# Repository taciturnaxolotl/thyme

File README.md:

# The thyme keyboard

> [!NOTE]
> If you want to build this yourself then go grab the files from the latest release!

## BOM

| Part                                                    | Quantity                                                                        | Price    | Link                                                                                                            | Description                                                                                 | Notes                                                   |
| ------------------------------------------------------- | ------------------------------------------------------------------------------- | -------- | --------------------------------------------------------------------------------------------------------------- | ------------------------------------------------------------------------------------------- | ------------------------------------------------------- |
| PCB                                                     | 1                                                                               | `$15.70` | [JLCPCB](https://jlcpcb.com)                                                                                    | 2-layer, 1.6mm, black, leaded Hasl                                                          | I wanted to get ENIG but that bumped the price by `$20` |
| Total `$15.70` + `$13.04` shipping                      |                                                                                 |          |                                                                                                                 |                                                                                             |                                                         |
|                                                         |                                                                                 |          |                                                                                                                 |                                                                                             |                                                         |
| Choc v1 switches                                        | 50                                                                              | `$25.00` | [Chosfox](https://chosfox.com/products/kailh-chocs?variant=42514648006850)                                      | pink variant: `20+-5 gf` linear                                                             | `$0.50` per switch                                      |
| Choc PG1350                                             | 50                                                                              | `$7.25`  | [Chosfox](https://chosfox.com/products/kailh-choc-switch-1350-hot-swap-sockets)                                 | hot swap sockets                                                                            | `$0.145` per socket                                     |
| 1u keycaps                                              | 40                                                                              | `$14.00` | [Chosfox](https://chosfox.com/collections/low-profile-keycaps/products/chocfox-cfx-choc-keycaps)                | White PBT low profile                                                                       | `$0.35` per keycap                                      |
| 1u homing keycaps                                       | 2                                                                               | `$0.80`  | [Chosfox](https://chosfox.com/collections/low-profile-keycaps/products/chocfox-cfx-choc-keycaps)                | White PBT low profile                                                                       | `$0.40` per keycap                                      |
| 1.5u keycaps                                            | 2                                                                               | `$1.65`  | [Chosfox](https://chosfox.com/collections/low-profile-keycaps/products/chocfox-cfx-choc-keycaps)                | White PBT low profile                                                                       | `$0.83` per keycap                                      |
| Total cost: `$48.70` + `$8` shipping                    |                                                                                 |          |                                                                                                                 | average of `$0.37` per keycap                                                               |                                                         |
|                                                         |                                                                                 |          |                                                                                                                 |                                                                                             |                                                         |
| SuperMini NRF52840 (Nice!Nano footprint)                | 2                                                                               | `$8.08`  | [AliExpress](https://www.aliexpress.us/item/3256805848952479.html)                                              | Wireless Microcontroller                                                                    | `$4.04` per MCU                                         |
| 301230 3.7V 110mAh LiPo Battery                         | 2                                                                               | `$7.50`  | [AliExpress](https://www.aliexpress.us/item/2255799987926232.html)                                              | the non jst ones are cheaper but the crimper is 60 bucks and there is no way im buying that | `$3.75` per battery                                     |
| Diodes                                                  | 42                                                                              | `$0.99`  | [Aliexpress](https://www.aliexpress.us/item/2255800939822415.html)                                              | 1N4148                                                                                      | `$0.01` per diode                                       |
| Machine Pins                                            | 1                                                                               | `$0.99`  | [AliExpress](https://www.aliexpress.us/item/3256805556329561.html)                                              | 26x2 needed to socket the two MCUs                                                          | comes in a 100 pack of 4 per header                     |
| Total cost: `$14.10` + `$6.52` shipping                 |                                                                                 |          |                                                                                                                 |                                                                                             |                                                         |
|                                                         |                                                                                 |          |                                                                                                                 |                                                                                             |                                                         |
| Power Switch                                            | 4                                                                               | `$0.39`  | [DigiKey](https://www.digikey.com/en/products/detail/same-sky-formerly-cui-devices/SLW-1277744-3A-N-D/24399208) | added an extra switch for each side as backup                                               | `$0.10` per switch                                      |
| JST PH 2.0mm 2-pin Connector                            | 4                                                                               | `$0.40`  | [DigiKey](https://www.digikey.com/en/products/detail/jst-sales-america-inc/S2B-PH-K-S/926626)                   |                                                                                             | `$0.10` per connector                                   |
| Total cost: `$1.96` + `$8.15` tarrif/sales tax/shipping | i cant find good matches for these on ali and shipping is ridiculous rn as well |          |                                                                                                                 |                                                                                             |                                                         |
|                                                         |                                                                                 |          |                                                                                                                 |
| Machine Sockets 2.54mm                                  | 1                                                                               | `$7.35`  | [Amazon](https://www.amazon.com/dp/B08Y8RB4BH)                                                                  | 26x2 needed to socket the two MCUs                                                          | comes in a 10 pack of 40x1 rows                         |

Total cost: `$123.52`

### Shipping / Tax / Tariffs / Per store shopping list

| Store      | Shipping                      | Subtotal | Total    | Items                                                                       |
| ---------- | ----------------------------- | -------- | -------- | --------------------------------------------------------------------------- |
| AliExpress | `$6.52`                       | `$14.20` | `$20.62` | 2x SuperMini NRF52840, Machine Pins, 2x LiPo Battery, 42x diodes            |
| DigiKey    | `$8.15` (tarrifs and tax too) | `$1.96`  | `$10.11` | 4x Power Switch, 4x JST Connector                                           |
| Chosfox    | `$8`                          | `$48.70` | `$56.70` | 50x Choc v1 switches, 40x 1u keycaps, 2x 1u homing keycaps, 2x 1.5u keycaps |
| JLCPCB     | `$13.04`                      | `$15.70` | `$28.74` | 1x PCB                                                                      |
| Amazon     | `$0`                          | `7.35`   | `$7.35`  | machine sockets                                                             |

## Schematics

## Build Notes

Panelization is the most annoying bit of this whole process. I was able to finally get it work work by using [`kikit`](https://yaqwsx.github.io/KiKit/latest/installation/intro/) to generate rails and tabs.

```bash
kikit panelize \
    --layout 'grid; rows: 1; cols: 1; space: 3mm;' \
    --tabs 'fixed; width: 3mm; vcount: 8;' \
    --cuts 'mousebites; drill: 0.5mm; spacing: 1mm; offset: 0.2mm; prolong: 0.5mm;' \
    --framing 'railstb; width: 5mm; space: 3mm; chamfer: 1mm;' \
    --tooling '3hole; hoffset: 2.5mm; voffset: 2.5mm; size: 1.5mm;' \
    --fiducials '3fid; hoffset: 5mm; voffset: 2.5mm; coppersize: 2mm; opening: 1mm;' \
    --post 'millradius: 1mm;' \
    --text 'simple; text: "THYME v1.14"; anchor: mt; voffset: 2mm;' \
    --text2 'simple; text: Created on {date} JLC Order: JLCJLCJLC; anchor: mb; voffset: -2.5mm; hjustify: center; vjustify: center;' \
    thyme.kicad_pcb panelization/panelized.kicad_pcb
```

Firmware is `zmk` and is maintained in the submodule [/zmk](https://github.com/taciturnaxolotl/thyme-module). The latest firmware build can be grabbed from [nightly.link/taciturnaxolotl/thyme-module/workflows/build](https://nightly.link/taciturnaxolotl/thyme-module/workflows/build/main) as a zip containing the left and right half `uf2` files.

The case was made in onshape and is available in [this document](https://cad.onshape.com/documents/eb30178d0af4291efc746ab6/w/0d165c7d0bf8d717a9598c9f/e/3dd4b0baac9c9ef14c8041ba?renderMode=0&uiState=67efb22294ee2703b96c81ea). The case is made of PLA and printed on an A1 mini. It is likely to change quite a bit once I get my pcb assembled and can fit test stuff. Evenentually I would like to add a top plate that attaches to the bottom with magnets and mill the whole case out of aluminum.

A major tool that helped with the research and organization of my thoughts was my [figjam board](https://www.figma.com/board/wyCQS9SeIG2Sutu5v6OT2m/thyme---split-mech-keyboard?node-id=0-1&t=SG0VuRAT0FkSCQlS-1)! I used it to keep track of all the resources I found and what parts I wanted to use. Once I got to actually picking specific parts I moved that to the bom table above.

<p align="center">
	<i><code>&copy 2025-present <a href="https://github.com/taciturnaxolotl">Kieran Klukas</a></code></i>
</p>

<p align="center">
	
</p>

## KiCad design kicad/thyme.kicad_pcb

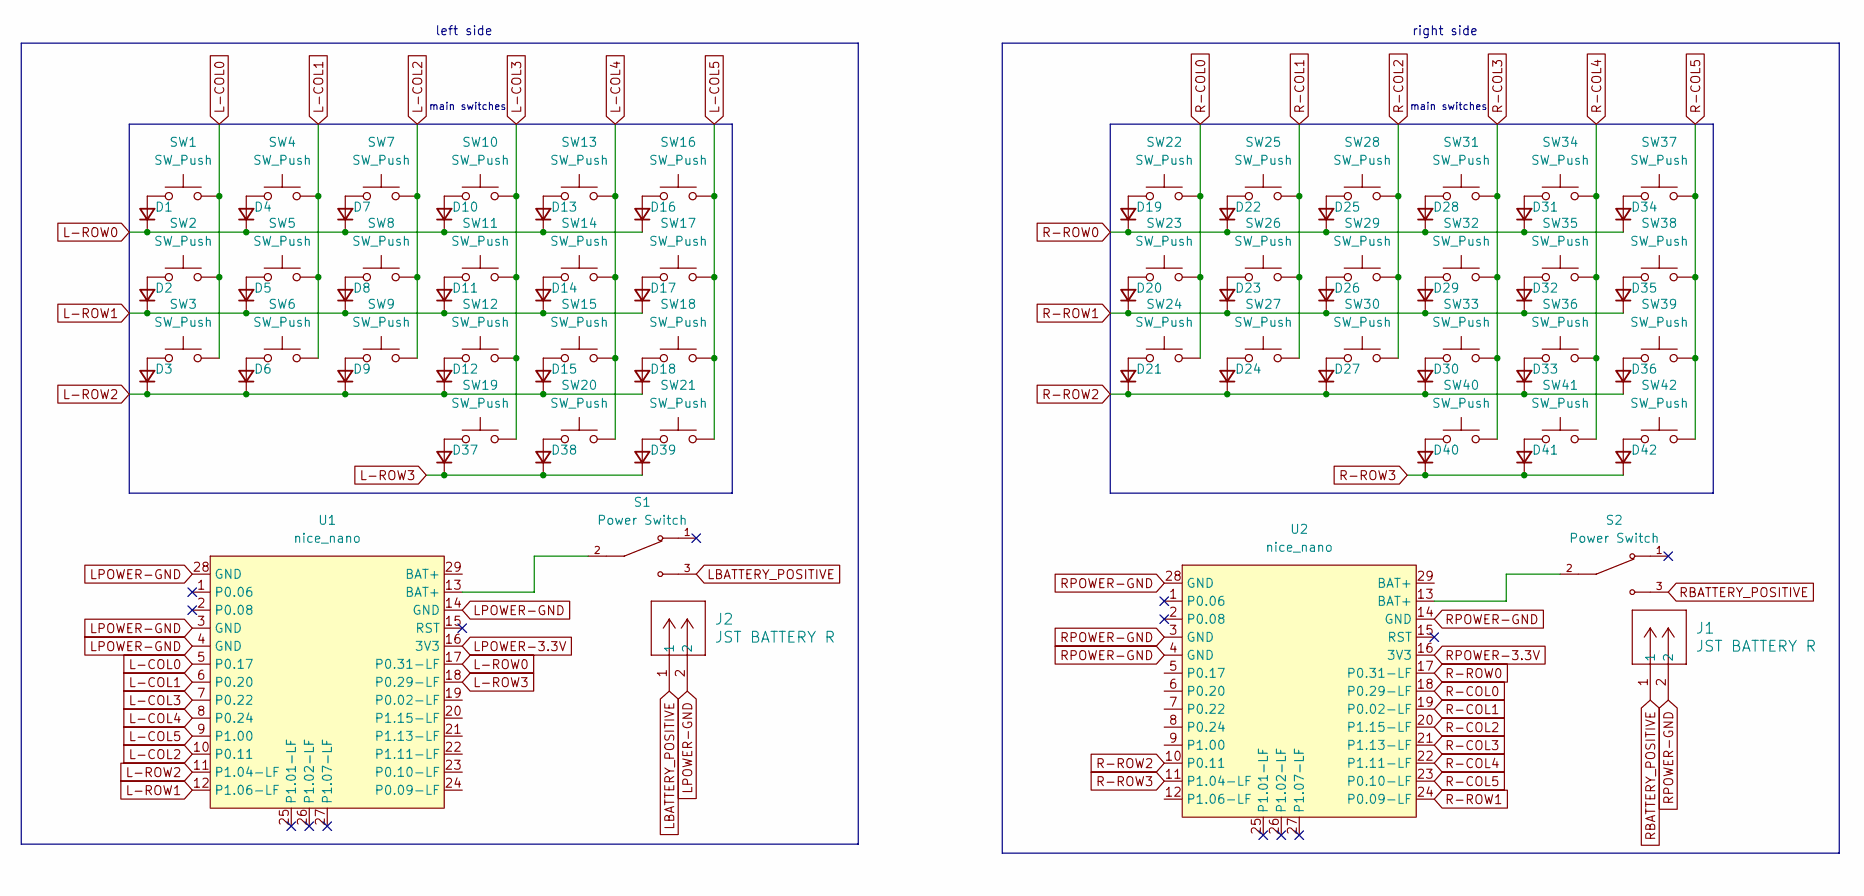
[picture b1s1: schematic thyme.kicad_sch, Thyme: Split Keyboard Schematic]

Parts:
D1, D2, D3, D4, D5, D6, D7, D8, D9, D10, D11, D12, D13, D14, D15, D16, D17, D18, D19, D20, D21, D22, D23, D24, D25, D26, D27, D28, D29, D30, D31, D32, D33, D34, D35, D36, D37, D38, D39, D40, D41, D42: D_Small; D_DO-35_SOD27_P7.62mm_Horizontal
J1, J2: JST BATTERY R; CONN_S2B-PH-K-S_JST
S1, S2: Power Switch; SW_SLW-1277744-3A-N-D; PARTREV 1.01
SW1, SW2, SW3, SW4, SW5, SW6, SW7, SW8, SW9, SW10, SW11, SW12, SW13, SW14, SW15, SW16, SW17, SW18, SW19, SW20, SW21, SW22, SW23, SW24, SW25, SW26, SW27, SW28, SW29, SW30, SW31, SW32, SW33, SW34, SW35, SW36, SW37, SW38, SW39, SW40, SW41, SW42: SW_Push; SW_Hotswap_Kailh_Choc_V1V2_1.00u
U1, U2: nice_nano; SuperMini NRF52840

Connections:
L-COL0: SW1.2, SW2.2, SW3.2, U1.5 (P0.17)
L-COL1: SW4.2, SW5.2, SW6.2, U1.6 (P0.20)
L-COL2: SW7.2, SW8.2, SW9.2, U1.10 (P0.11)
L-COL3: SW10.2, SW11.2, SW12.2, SW19.2, U1.7 (P0.22)
L-COL4: SW13.2, SW14.2, SW15.2, SW20.2, U1.8 (P0.24)
L-COL5: SW16.2, SW17.2, SW18.2, SW21.2, U1.9 (P1.00)
L-ROW0: D1.1 (K), D4.1 (K), D7.1 (K), D10.1 (K), D13.1 (K), D16.1 (K), U1.17 (P0.31-LF)
L-ROW1: D2.1 (K), D5.1 (K), D8.1 (K), D11.1 (K), D14.1 (K), D17.1 (K), U1.12 (P1.06-LF)
L-ROW2: D3.1 (K), D6.1 (K), D9.1 (K), D12.1 (K), D15.1 (K), D18.1 (K), U1.11 (P1.04-LF)
L-ROW3: D37.1 (K), D38.1 (K), D39.1 (K), U1.18 (P0.29-LF)
LBATTERY_POSITIVE: J2.1, S1.3
LPOWER-3.3V: U1.16 (3V3)
LPOWER-GND: J2.2, U1.3 (GND), U1.4 (GND), U1.14 (GND), U1.28 (GND)
unnamed: D1.2 (A), SW1.1
unnamed: D2.2 (A), SW2.1
unnamed: D3.2 (A), SW3.1
unnamed: D4.2 (A), SW4.1
unnamed: D5.2 (A), SW5.1
unnamed: D6.2 (A), SW6.1
unnamed: D7.2 (A), SW7.1
unnamed: D8.2 (A), SW8.1
unnamed: D9.2 (A), SW9.1
unnamed: D10.2 (A), SW10.1
unnamed: D11.2 (A), SW11.1
unnamed: D12.2 (A), SW12.1
unnamed: D13.2 (A), SW13.1
unnamed: D14.2 (A), SW14.1
unnamed: D15.2 (A), SW15.1
unnamed: D16.2 (A), SW16.1
unnamed: D17.2 (A), SW17.1
unnamed: D18.2 (A), SW18.1
unnamed: D19.2 (A), SW22.1
unnamed: D20.2 (A), SW23.1
unnamed: D21.2 (A), SW24.1
unnamed: D22.2 (A), SW25.1
unnamed: D23.2 (A), SW26.1
unnamed: D24.2 (A), SW27.1
unnamed: D25.2 (A), SW28.1
unnamed: D26.2 (A), SW29.1
unnamed: D27.2 (A), SW30.1
unnamed: D28.2 (A), SW31.1
unnamed: D29.2 (A), SW32.1
unnamed: D30.2 (A), SW33.1
unnamed: D31.2 (A), SW34.1
unnamed: D32.2 (A), SW35.1
unnamed: D33.2 (A), SW36.1
unnamed: D34.2 (A), SW37.1
unnamed: D35.2 (A), SW38.1
unnamed: D36.2 (A), SW39.1
unnamed: D37.2 (A), SW19.1
unnamed: D38.2 (A), SW20.1
unnamed: D39.2 (A), SW21.1
unnamed: D40.2 (A), SW40.1
unnamed: D41.2 (A), SW41.1
unnamed: D42.2 (A), SW42.1
unnamed: S1.2, U1.13 (BAT+)
unnamed: S2.2, U2.13 (BAT+)
R-COL0: SW22.2, SW23.2, SW24.2, U2.18 (P0.29-LF)
R-COL1: SW25.2, SW26.2, SW27.2, U2.19 (P0.02-LF)
R-COL2: SW28.2, SW29.2, SW30.2, U2.20 (P1.15-LF)
R-COL3: SW31.2, SW32.2, SW33.2, SW40.2, U2.21 (P1.13-LF)
R-COL4: SW34.2, SW35.2, SW36.2, SW41.2, U2.22 (P1.11-LF)
R-COL5: SW37.2, SW38.2, SW39.2, SW42.2, U2.23 (P0.10-LF)
R-ROW0: D19.1 (K), D22.1 (K), D25.1 (K), D28.1 (K), D31.1 (K), D34.1 (K), U2.17 (P0.31-LF)
R-ROW1: D20.1 (K), D23.1 (K), D26.1 (K), D29.1 (K), D32.1 (K), D35.1 (K), U2.24 (P0.09-LF)
R-ROW2: D21.1 (K), D24.1 (K), D27.1 (K), D30.1 (K), D33.1 (K), D36.1 (K), U2.10 (P0.11)
R-ROW3: D40.1 (K), D41.1 (K), D42.1 (K), U2.11 (P1.04-LF)
RBATTERY_POSITIVE: J1.1, S2.3
RPOWER-3.3V: U2.16 (3V3)
RPOWER-GND: J1.2, U2.3 (GND), U2.4 (GND), U2.14 (GND), U2.28 (GND)

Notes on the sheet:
left side
main switches
right side

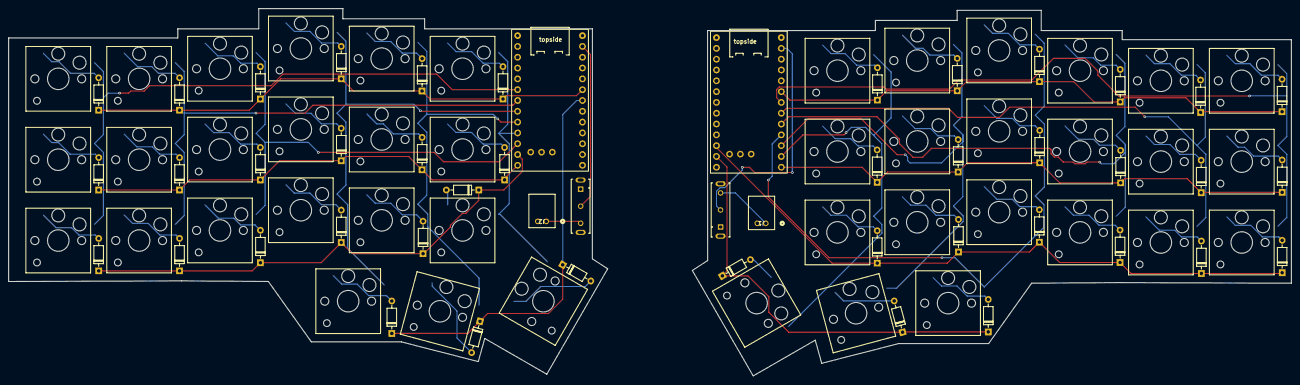
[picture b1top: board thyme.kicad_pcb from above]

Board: 2 copper layers, 301.4 x 86.3 mm, 90 parts (0 on the bottom side), 68 nets.

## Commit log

2025-03-09 docs: inital setup
2025-03-25 feat: add schematic v0.1
2025-03-28 feat: add the jst power connections and connect nets
2025-03-28 bug: fix row 5 being unconnected
2025-03-28 chore: split power into left and right and add no connects
2025-03-30 chore: move around footprints
2025-03-30 feat: align key switches in pcb
2025-03-31 feat: arrange switches and add edge cuts
2025-03-31 feat: place diodes
2025-03-31 feat: add new jst connector and route the board
2025-03-31 feat: add 3d models
2025-03-31 feat: add images
2025-03-31 [ImgBot] Optimize images
    *Total -- 2,261.65kb -> 1,587.35kb (29.81%)
    /.github/images/schematic.svg -- 2,254.90kb -> 1,580.68kb (29.9%)
    /.github/images/tanabata.svg -- 6.75kb -> 6.67kb (1.24%)
2025-03-31 feat: move jst to top for machine pins
2025-03-31 feat: move to jst tht connector and new switches
2025-03-31 feat: add panelization
2025-03-31 feat: add panelization schematic and instructions
2025-04-01 chore: move jst to allow room for 1.75u keycaps
2025-04-01 feat: add bom
2025-04-01 docs: organize bom
2025-04-04 feat: use same cutout for both halves
2025-04-04 docs: add blueprint
2025-04-04 feat: update blueprint
2025-04-04 [ImgBot] Optimize images
    *Total -- 4,728.86kb -> 3,465.49kb (26.72%)
    /.github/images/schematic.svg -- 2,261.43kb -> 1,586.05kb (29.86%)
    /.github/images/pcb.svg -- 2,460.69kb -> 1,872.77kb (23.89%)
    /.github/images/tanabata.svg -- 6.75kb -> 6.67kb (1.24%)
2025-04-04 feat: add cad
2025-04-04 feat: use another row instead of col 7
2025-04-04 feat: add zmk config
2025-04-04 chore: add zmk build working dir
2025-04-04 chore: remove zmk config
2025-04-04 feat: add zmk submodule
2025-04-04 chore: use http submodule url
2025-04-04 feat: add main branch to submodules
2025-04-04 docs: add firmware
2025-04-04 docs: talk about figjam
2025-04-10 feat: redesign edge cuts and key spacing
2025-04-10 feat: update cad design for v16
2025-04-10 docs: make keycaps 1.5u instead of 1.75u
2025-04-10 feat: add stabilizers
2025-04-10 feat: add hot swap sockets
2025-04-10 docs: add hot swap sockets
2025-04-10 [ImgBot] Optimize images
    /.github/images/schematic.svg -- 1,315.29kb -> 1,232.32kb (6.31%)
2025-04-10 [ImgBot] Optimize images
    /.github/images/figjam.png -- 760.81kb -> 749.56kb (1.48%)
2025-04-15 docs: add link for kikit
2025-05-03 feat: remove uncessessary bits of footprint
2025-10-16 chore: update bom
2025-10-16 chore: remove cliff
2025-10-16 chore: add info block
2025-10-16 chore: update gitignore
2025-10-16 docs: update bom again
2025-10-17 docs: make bom cheaper
2025-11-12 feat: move to 6 connectors and remove silkscreen lables
